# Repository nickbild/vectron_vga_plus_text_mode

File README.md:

# Vectron VGA Plus Text Mode

Vectron VGA Plus Text Mode simplifies displaying text with retro computers and microcontrollers by hiding the pixel-level details.  Supply only row and column positions, and an ASCII character code, to write text to a 40x30 character VGA display.

## How It Works

Vectron VGA Plus Text Mode accepts row, column, and character codes into 8-bit flip flop registers from external systems.  Using a 6502 processor and pre-programmed ROM chip ([code here](https://github.com/nickbild/vectron_vga_plus_text_mode/blob/main/os.asm)), these values are translated into a series of pixels to be drawn at x,y coordinates on the screen.  Both the program, and the library of available ASCII characters are stored in the ROM.  Instructions to draw each pixel are stored in 8-bit flip flop output registers where they can interface with and control a [Vectron VGA Plus](https://github.com/nickbild/vectron_vga_plus) VGA adapter.  Text Mode also handles initialization of a blank screen on the VGA adapter on startup.

To write a single 8x8 character to the screen without Text Mode would require writing 64 individual pixels, and performing all of the associated instructions and data transformations.  This would keep a typical 6502 computer pretty busy just writing to the screen, not to mention all of the other things the computer needs to do.  Text Mode allows for the same result with just a few instructions from the interfacing device.

At the heart of the design is a 65C02 processor to handle the somewhat complex calculations that would be difficult to perform with only logic chips, and would require a high part count.  I think using a microprocessor in this board is well within the bounds of being acceptable for a pure retro computing device, considering that the Commodore 1541 disk drive, for example, also had its own 6502 to handle processing.

An Arudino sketch that can be used to write characters using Text Mode [is here](https://github.com/nickbild/vectron_vga_plus_text_mode/tree/main/ardunio_tester).  KiCad design files are [available here](https://github.com/nickbild/vectron_vga_plus_text_mode/tree/main/kicad).  You will also need a [Vectron VGA Plus](https://github.com/nickbild/vectron_vga_plus) VGA adapter, which Text Mode was designed to work with.

## Media

Vectron VGA Plus Text Mode:

Vectron VGA Plus Text Mode attached to Vectron VGA Plus, with an Arduino Mega 2560 requesting the characters to be written on screen:

All characters in a repeating pattern:

Text mode interface:

Breadboard prototype (with a few components removed to place on the PCB):

## Bill of Materials

- 1 x WDC 65C02 processor
- 1 x AS6C62256A-70PCN 32KB RAM
- 1 x AT28C256-15PU 32KB ROM
- 1 x 8 MHz oscillator
- 4 x 3.3k ohm resistors
- 2 x 220 uF capacitors
- 1 x push button
- 2 x 7432
- 1 x 7408
- 1 x 7404
- 2 x 74682
- 1 x 74154
- 8 x 74374
- Female headers
- PCB ([KiCad design files](https://github.com/nickbild/vectron_vga_plus_text_mode/tree/main/kicad))

## About the Author

[Nick A. Bild, MS](https://nickbild79.firebaseapp.com/#!/)

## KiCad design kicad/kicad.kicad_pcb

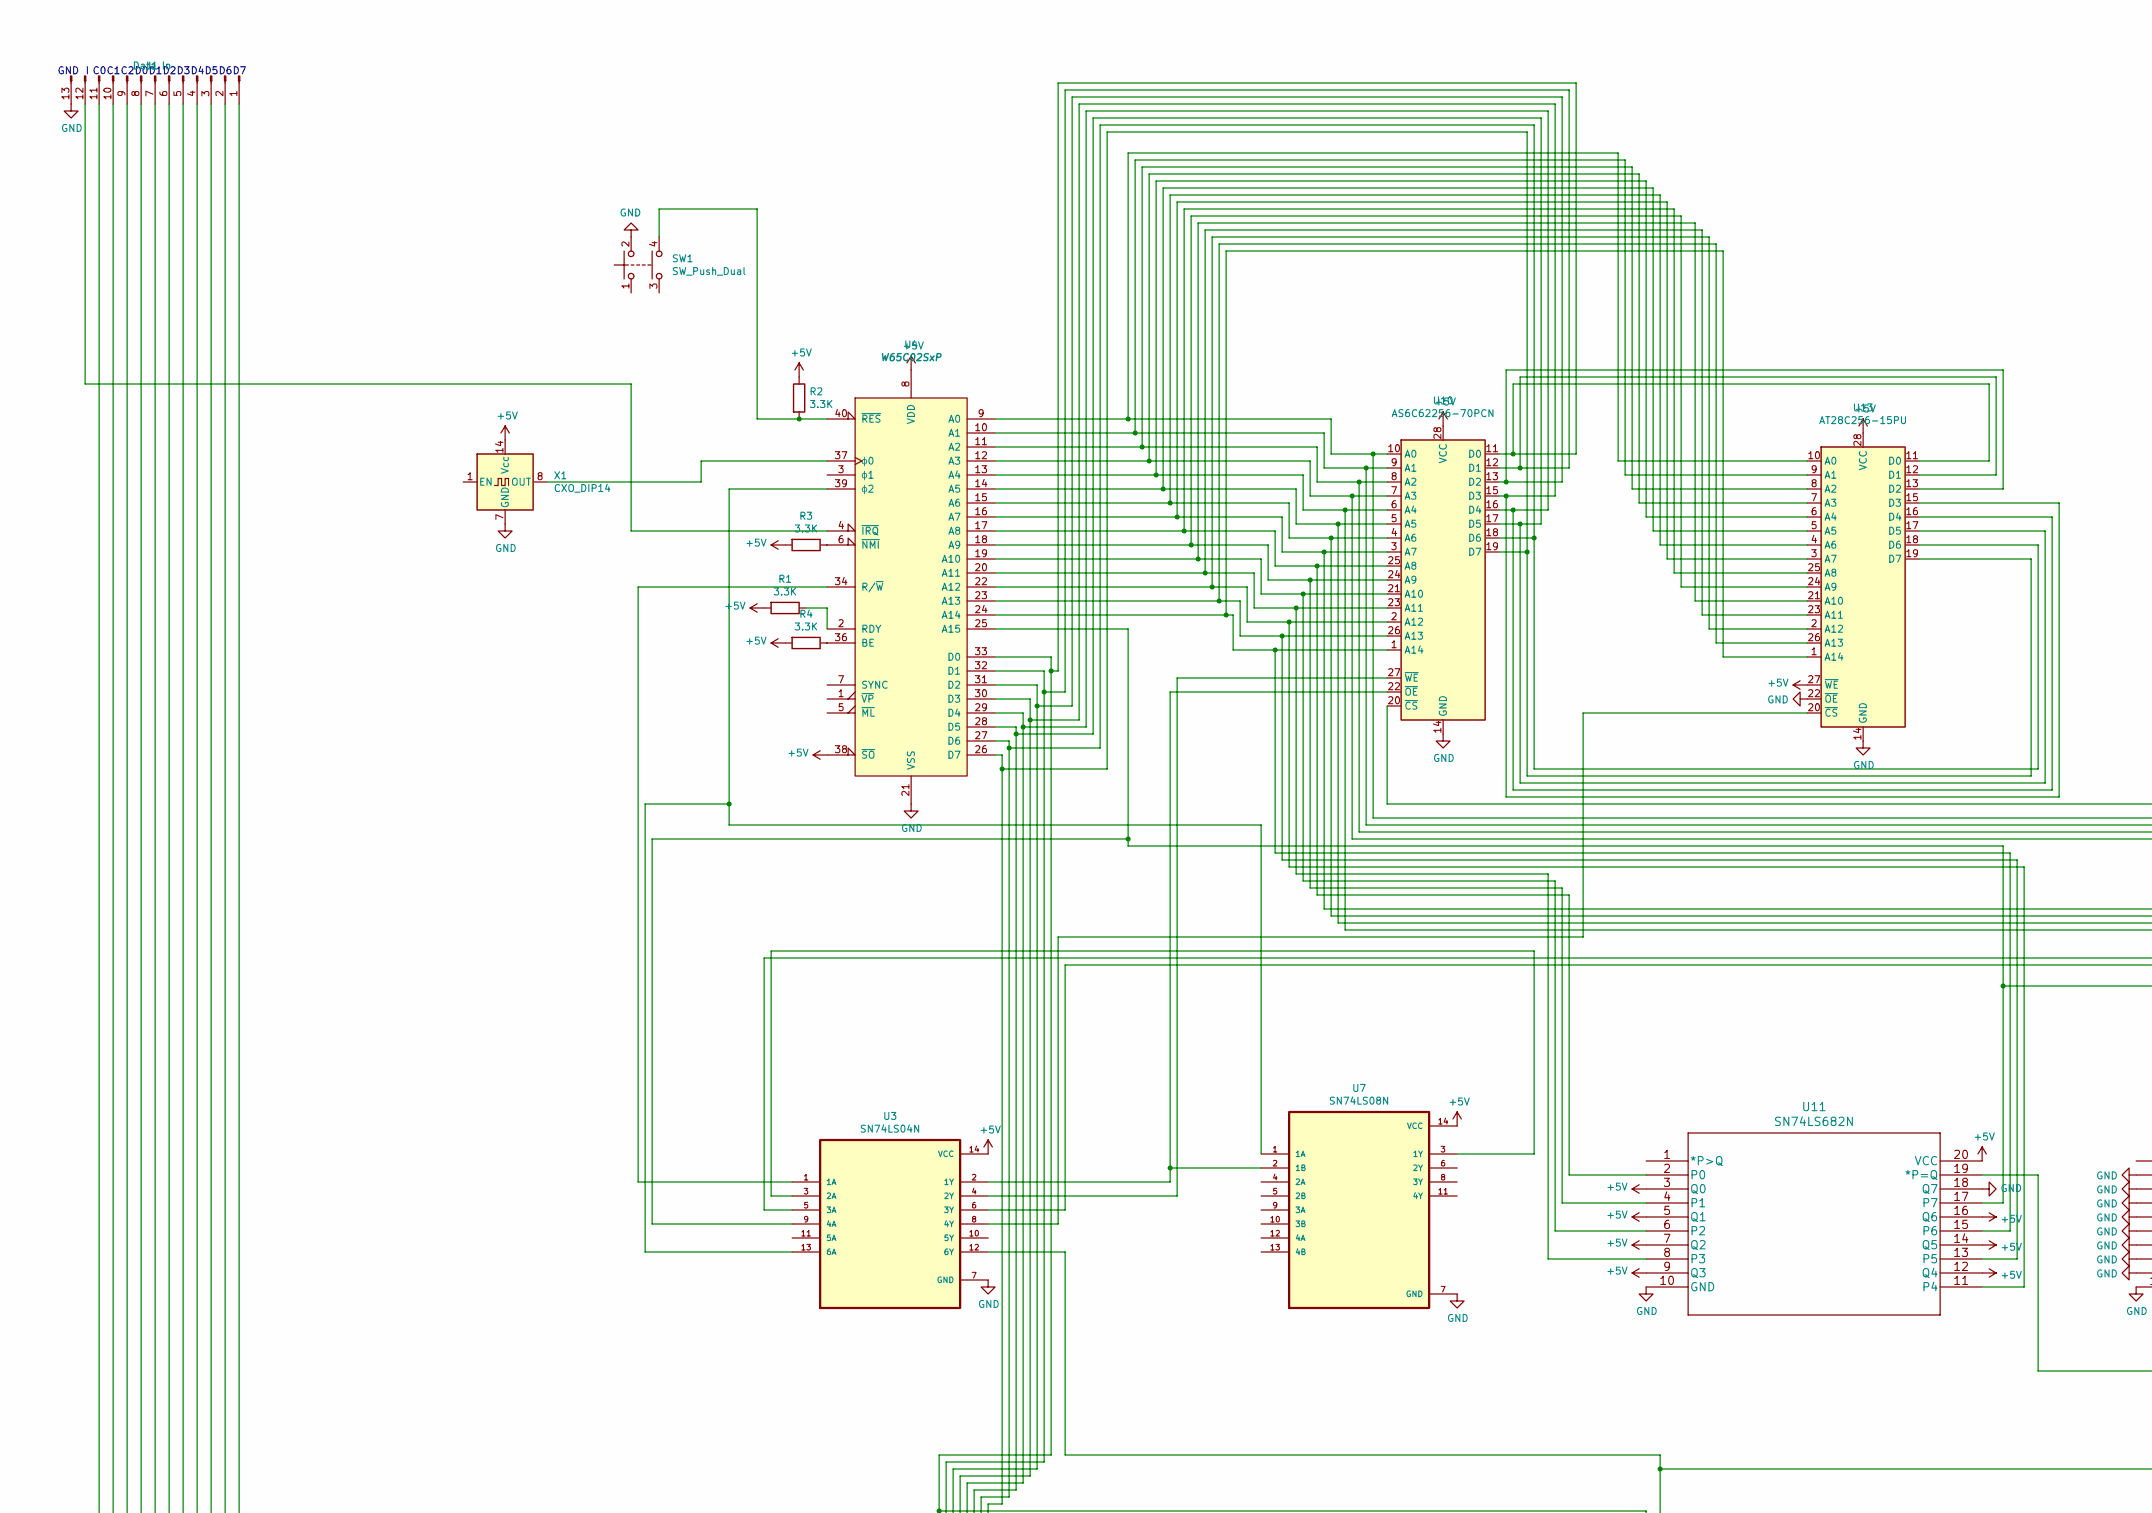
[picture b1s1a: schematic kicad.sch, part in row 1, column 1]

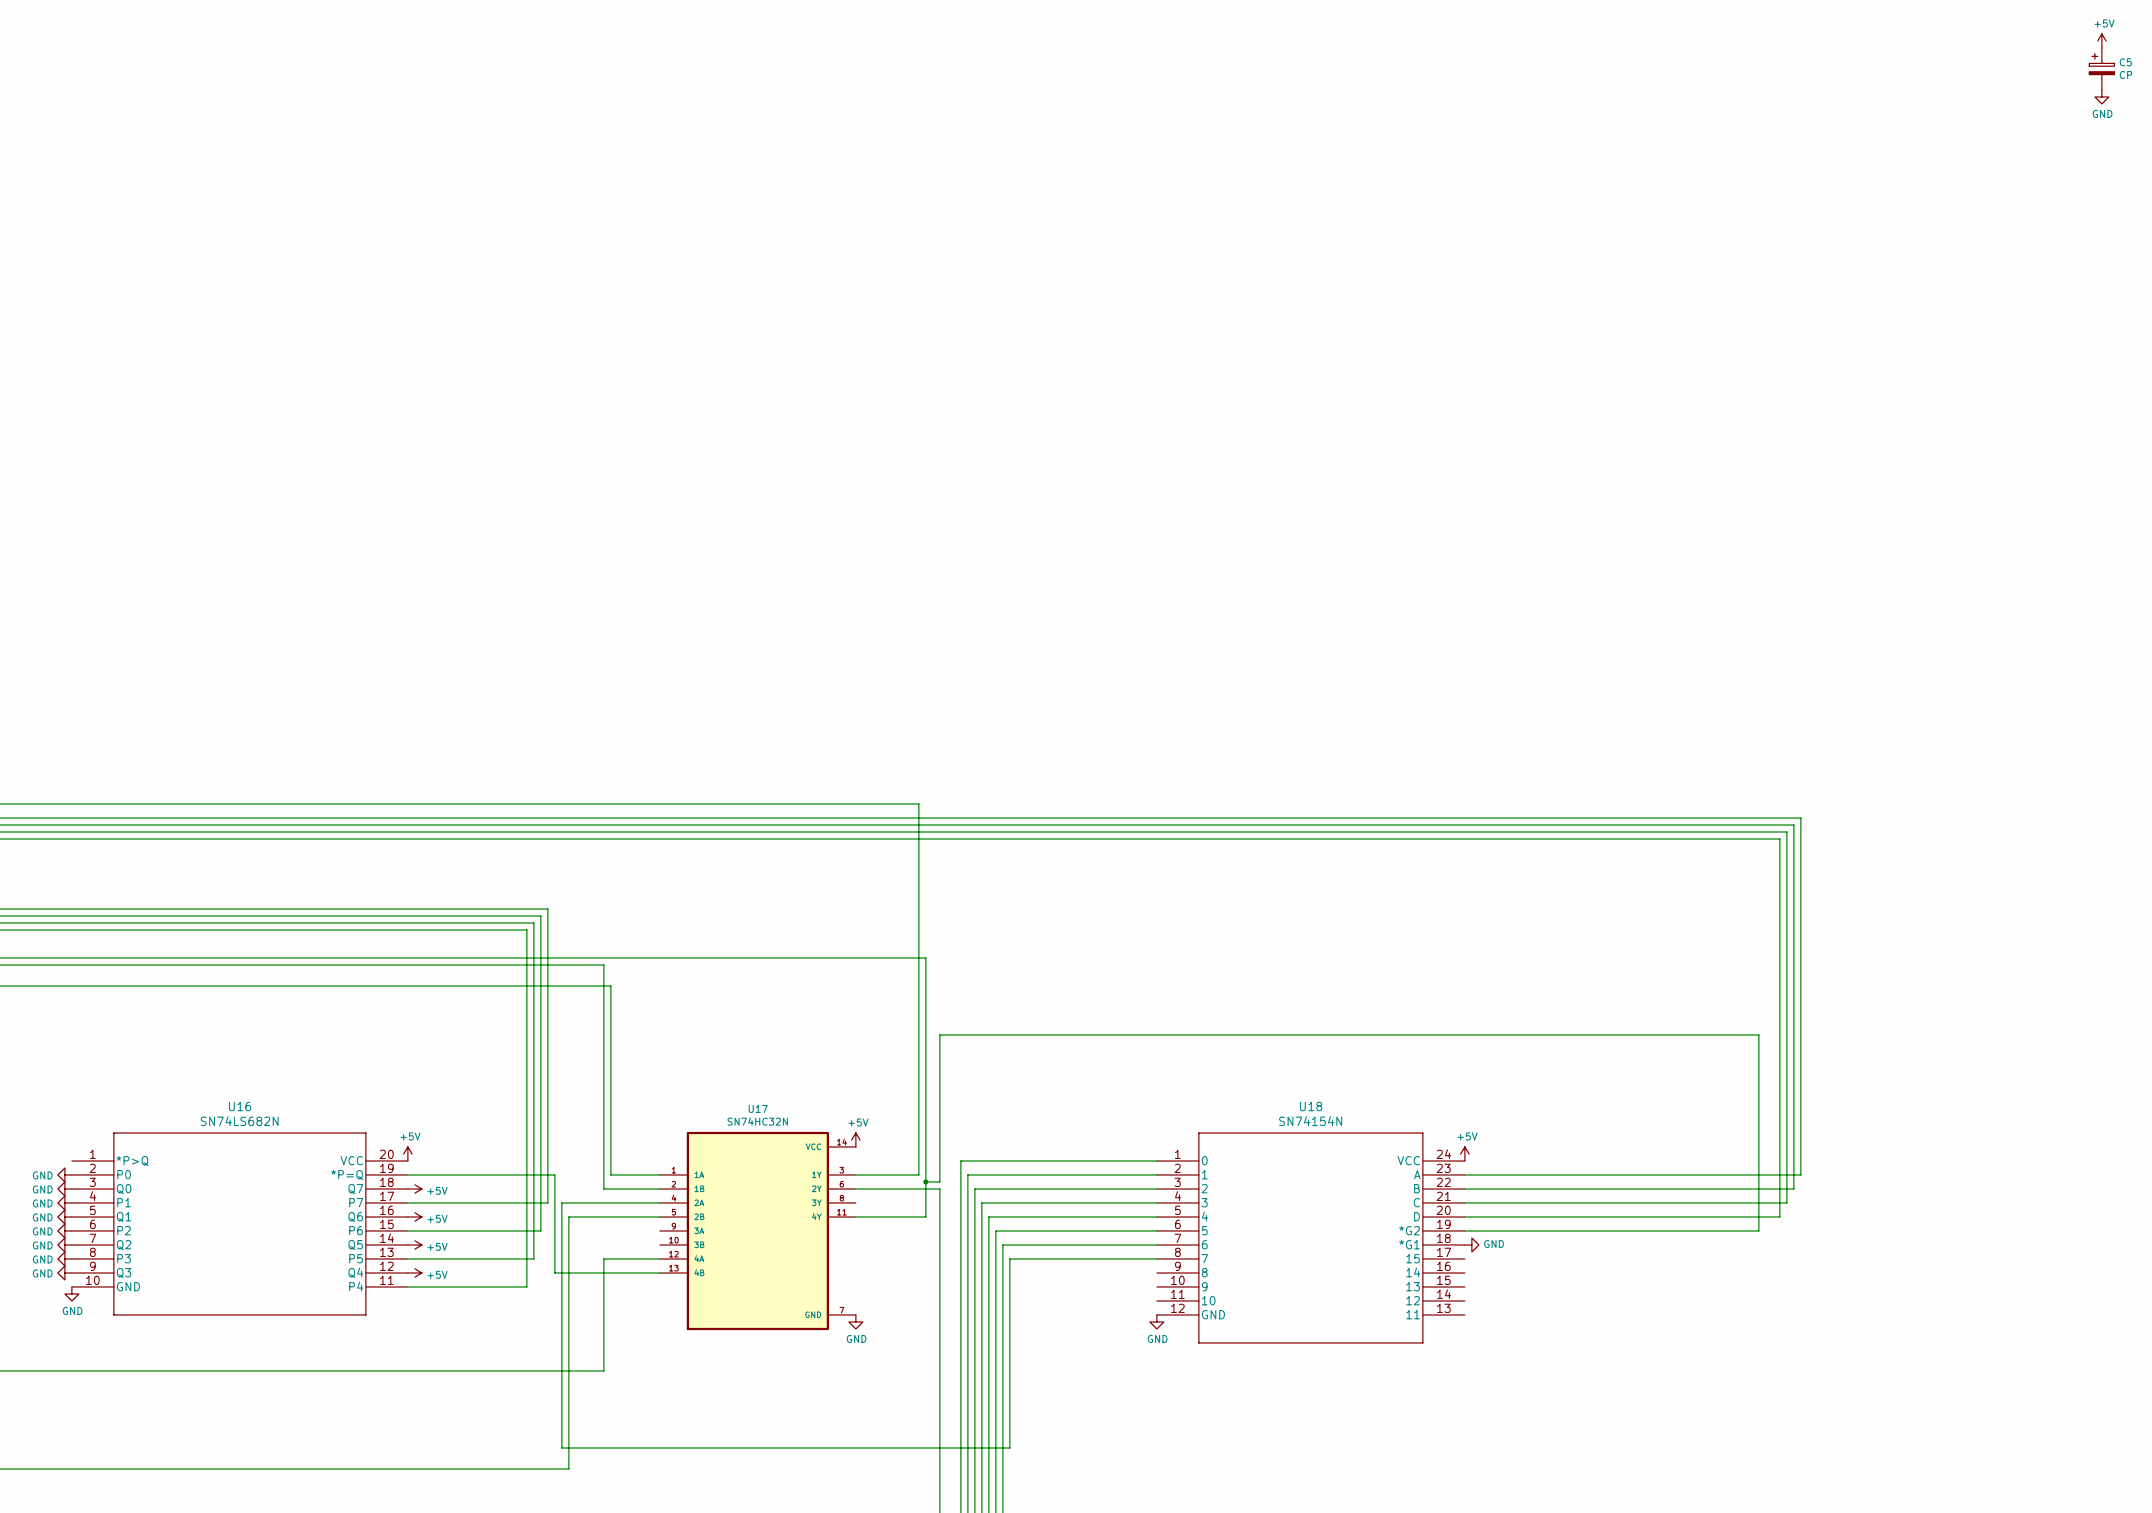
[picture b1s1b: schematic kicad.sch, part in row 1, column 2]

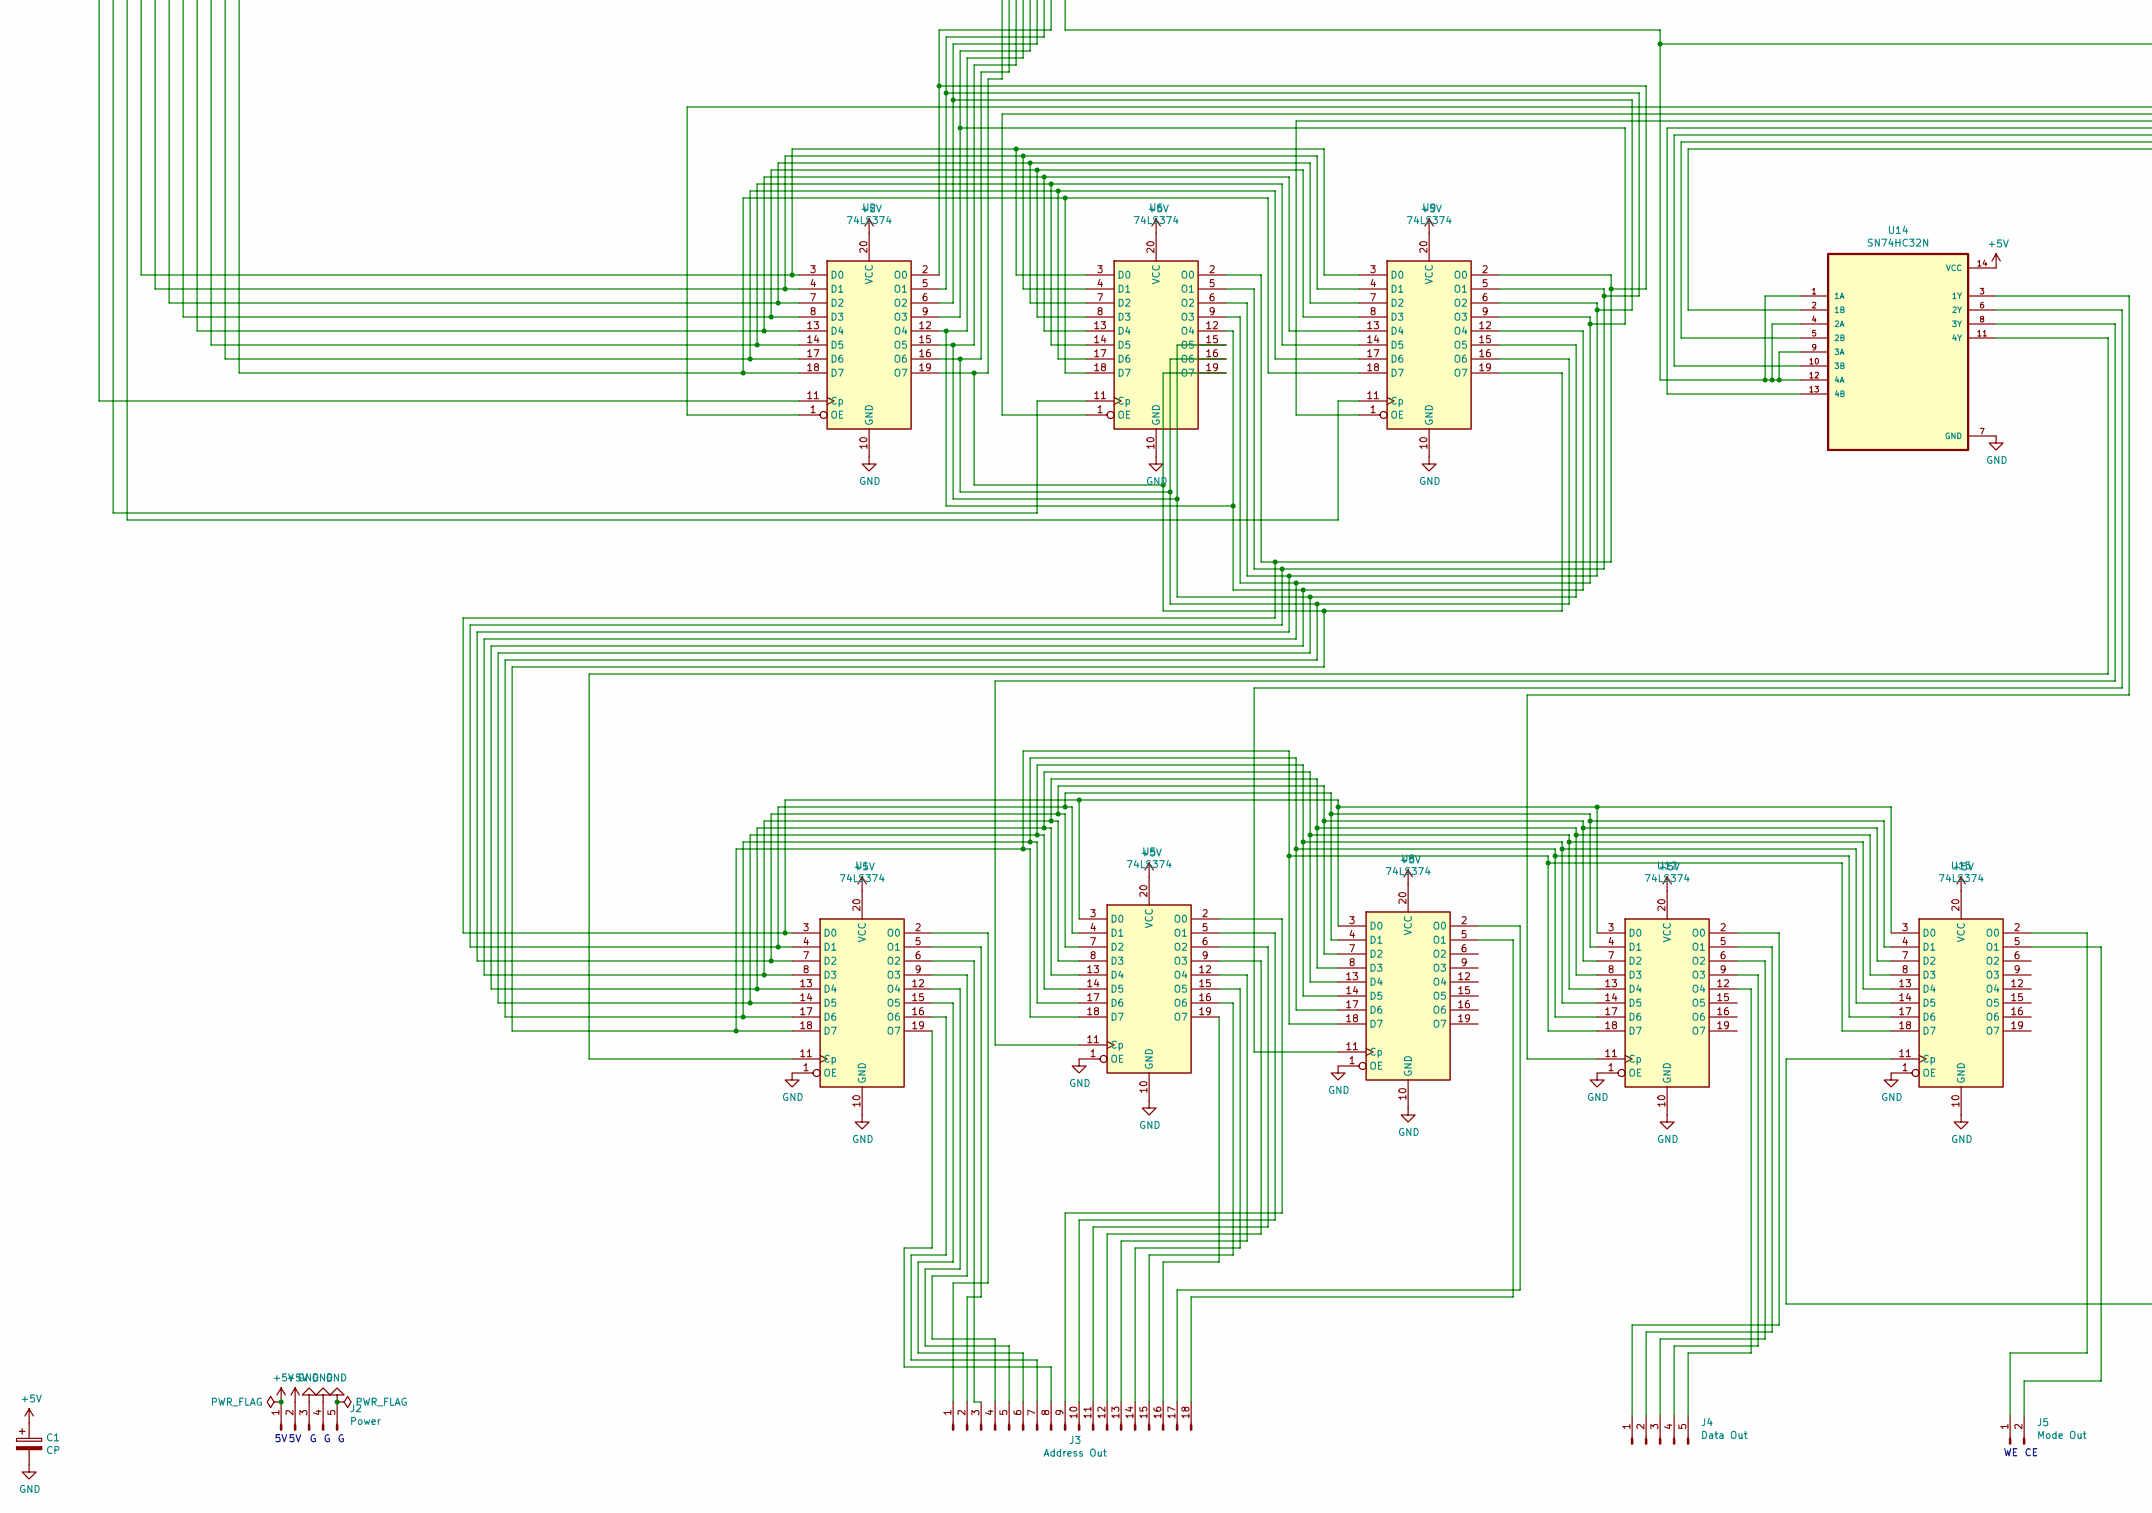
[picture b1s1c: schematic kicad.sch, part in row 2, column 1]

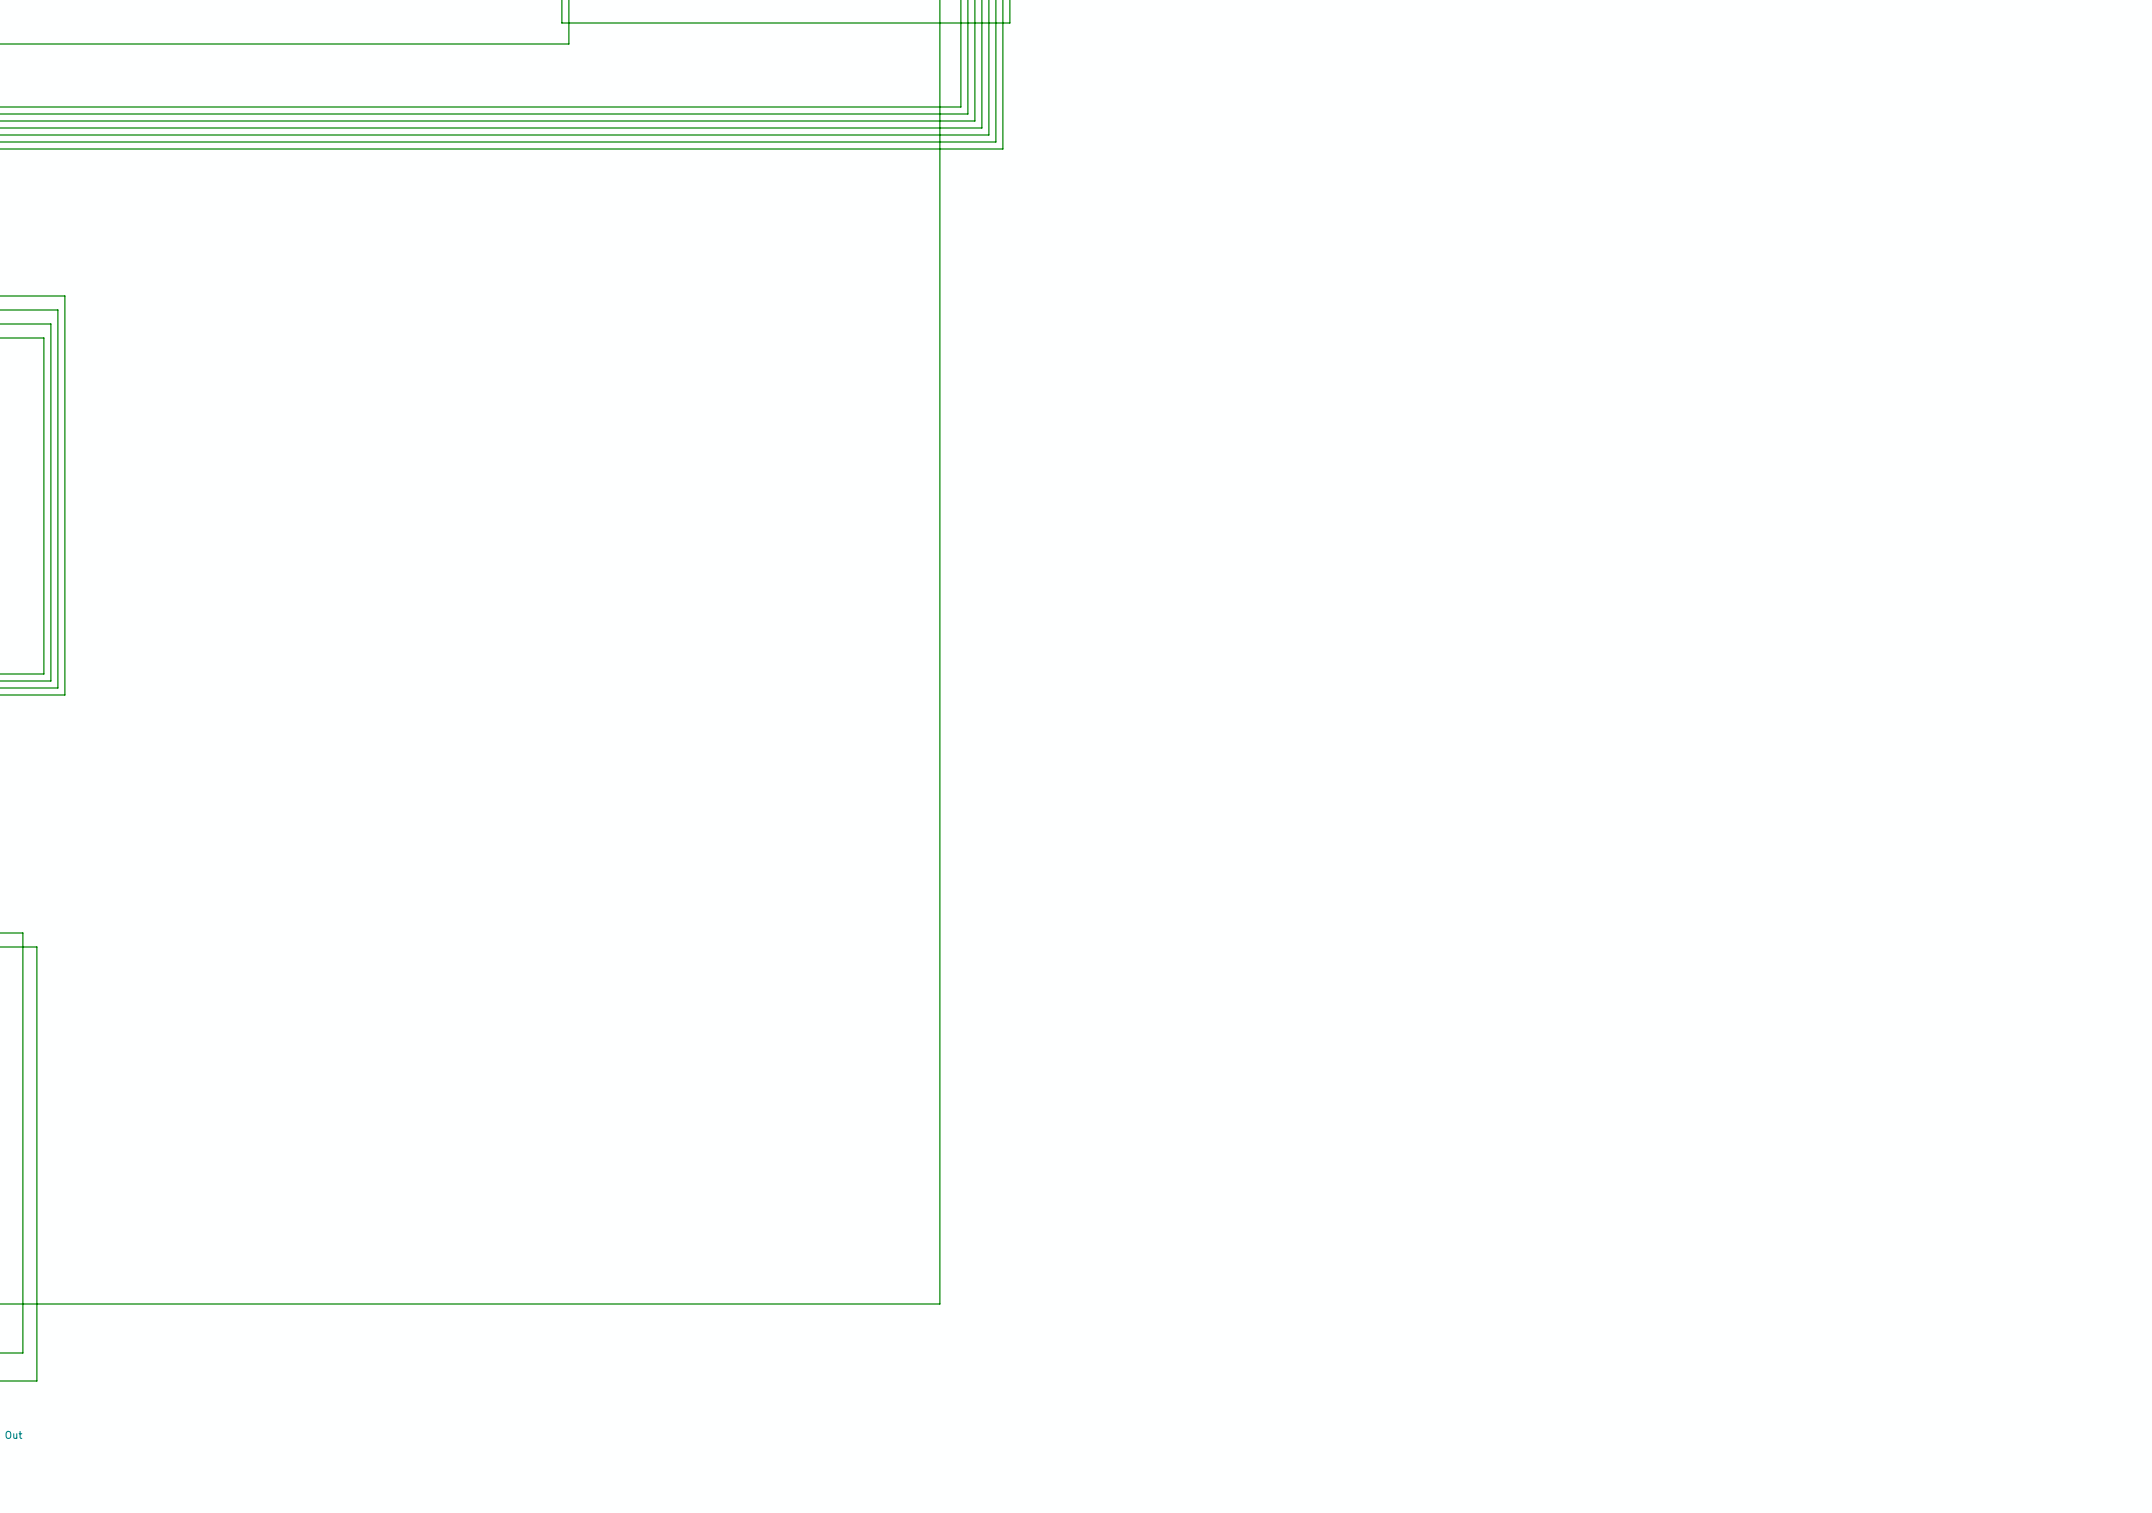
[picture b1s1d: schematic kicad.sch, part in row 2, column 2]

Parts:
C1, C5: CP; CP_Radial_D12.5mm_P7.50mm
J1: Data In; PinHeader_1x13_P2.54mm_Horizontal
J2: Power; PinHeader_1x05_P2.54mm_Horizontal
J3: Address Out; PinHeader_1x18_P2.54mm_Horizontal
J4: Data Out; PinHeader_1x05_P2.54mm_Horizontal
J5: Mode Out; PinHeader_1x02_P2.54mm_Horizontal
R1, R2, R3, R4: 3.3K; R_Axial_DIN0207_L6.3mm_D2.5mm_P10.16mm_Horizontal
SW1: SW_Push_Dual; SW_TH_Tactile_Omron_B3F-10xx
U1, U2, U5, U6, U8, U9, U12, U15: 74LS374; DIP-20_W7.62mm
U3: SN74LS04N; DIP-14_W7.62mm
U4: W65C02SxP; DIP-40_W15.24mm
U7: SN74LS08N; DIP-14_W7.62mm
U10: AS6C62256-70PCN; DIP-28_W15.24mm
U11, U16: SN74LS682N; DIP-20_W7.62mm
U13: AT28C256-15PU; DIP-28_W15.24mm
U14, U17: SN74HC32N; DIP-14_W7.62mm
U18: SN74154N; DIP-24_W15.24mm
X1: CXO_DIP14; Oscillator_DIP-14

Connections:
+5V: C1.1, C5.1, J2.1, J2.2, R1.2, R2.1, R3.2, R4.2, U1.20 (VCC), U2.20 (VCC), U3.14 (VCC), U4.8 (VDD), U4.38 (~SO), U5.20 (VCC), U6.20 (VCC), U7.14 (VCC), U8.20 (VCC), U9.20 (VCC), U10.28 (VCC), U11.3 (Q0), U11.5 (Q1), U11.7 (Q2), U11.9 (Q3), U11.12 (Q4), U11.14 (Q5), U11.16 (Q6), U11.20 (VCC), U12.20 (VCC), U13.27 (~WE), U13.28 (VCC), U14.14 (VCC), U15.20 (VCC), U16.12 (Q4), U16.14 (Q5), U16.16 (Q6), U16.18 (Q7), U16.20 (VCC), U17.14 (VCC), U18.24 (VCC), X1.14 (Vcc)
GND: C1.2, C5.2, J1.13, J2.3, J2.4, J2.5, SW1.2, U1.1 (OE), U1.10 (GND), U2.10 (GND), U3.7 (GND), U4.21 (VSS), U5.1 (OE), U5.10 (GND), U6.10 (GND), U7.7 (GND), U8.1 (OE), U8.10 (GND), U9.10 (GND), U10.14 (GND), U11.10 (GND), U11.18 (Q7), U12.1 (OE), U12.10 (GND), U13.14 (GND), U13.22 (~OE), U14.7 (GND), U15.1 (OE), U15.10 (GND), U16.2 (P0), U16.3 (Q0), U16.4 (P1), U16.5 (Q1), U16.6 (P2), U16.7 (Q2), U16.8 (P3), U16.9 (Q3), U16.10 (GND), U17.7 (GND), U18.12 (GND), U18.18 (*G1), X1.7 (GND)
unnamed: J1.1, U2.18 (D7), U6.18 (D7), U9.18 (D7)
unnamed: J1.2, U2.17 (D6), U6.17 (D6), U9.17 (D6)
unnamed: J1.3, U2.14 (D5), U6.14 (D5), U9.14 (D5)
unnamed: J1.4, U2.13 (D4), U6.13 (D4), U9.13 (D4)
unnamed: J1.5, U2.8 (D3), U6.8 (D3), U9.8 (D3)
unnamed: J1.6, U2.7 (D2), U6.7 (D2), U9.7 (D2)
unnamed: J1.7, U2.4 (D1), U6.4 (D1), U9.4 (D1)
unnamed: J1.8, U2.3 (D0), U6.3 (D0), U9.3 (D0)
unnamed: J1.9, U9.11 (Cp)
unnamed: J1.10, U6.11 (Cp)
unnamed: J1.11, U2.11 (Cp)
unnamed: J1.12, U4.4 (~IRQ)
unnamed: J3.1, U1.2 (O0)
unnamed: J3.2, U1.5 (O1)
unnamed: J3.3, U1.6 (O2)
unnamed: J3.4, U1.9 (O3)
unnamed: J3.5, U1.12 (O4)
unnamed: J3.6, U1.15 (O5)
unnamed: J3.7, U1.16 (O6)
unnamed: J3.8, U1.19 (O7)
unnamed: J3.9, U5.2 (O0)
unnamed: J3.10, U5.5 (O1)
unnamed: J3.11, U5.6 (O2)
unnamed: J3.12, U5.9 (O3)
unnamed: J3.13, U5.12 (O4)
unnamed: J3.14, U5.15 (O5)
unnamed: J3.15, U5.16 (O6)
unnamed: J3.16, U5.19 (O7)
unnamed: J3.17, U8.2 (O0)
unnamed: J3.18, U8.5 (O1)
unnamed: J4.1, U12.2 (O0)
unnamed: J4.2, U12.5 (O1)
unnamed: J4.3, U12.6 (O2)
unnamed: J4.4, U12.9 (O3)
unnamed: J4.5, U12.12 (O4)
unnamed: J5.1, U15.2 (O0)
unnamed: J5.2, U15.5 (O1)
unnamed: R1.1, U4.2 (RDY)
unnamed: R2.2, SW1.4, U4.40 (~RES)
unnamed: R3.1, U4.6 (~NMI)
unnamed: R4.1, U4.36 (BE)
unnamed: U1.3 (D0), U2.2 (O0), U4.33 (D0), U5.3 (D0), U6.2 (O0), U8.3 (D0), U9.2 (O0), U10.11 (D0), U12.3 (D0), U13.11 (D0), U15.3 (D0)
unnamed: U1.4 (D1), U2.5 (O1), U4.32 (D1), U5.4 (D1), U6.5 (O1), U8.4 (D1), U9.5 (O1), U10.12 (D1), U12.4 (D1), U13.12 (D1), U15.4 (D1)
unnamed: U1.7 (D2), U2.6 (O2), U4.31 (D2), U5.7 (D2), U6.6 (O2), U8.7 (D2), U9.6 (O2), U10.13 (D2), U12.7 (D2), U13.13 (D2), U15.7 (D2)
unnamed: U1.8 (D3), U2.9 (O3), U4.30 (D3), U5.8 (D3), U6.9 (O3), U8.8 (D3), U9.9 (O3), U10.15 (D3), U12.8 (D3), U13.15 (D3), U15.8 (D3)
unnamed: U1.11 (Cp), U14.11 (4Y)
unnamed: U1.13 (D4), U2.12 (O4), U4.29 (D4), U5.13 (D4), U6.12 (O4), U8.13 (D4), U9.12 (O4), U10.16 (D4), U12.13 (D4), U13.16 (D4), U15.13 (D4)
unnamed: U1.14 (D5), U2.15 (O5), U4.28 (D5), U5.14 (D5), U6.15 (O5), U8.14 (D5), U9.15 (O5), U10.17 (D5), U12.14 (D5), U13.17 (D5), U15.14 (D5)
unnamed: U1.17 (D6), U2.16 (O6), U4.27 (D6), U5.17 (D6), U6.16 (O6), U8.17 (D6), U9.16 (O6), U10.18 (D6), U12.17 (D6), U13.18 (D6), U15.17 (D6)
unnamed: U1.18 (D7), U2.19 (O7), U4.26 (D7), U5.18 (D7), U6.19 (O7), U8.18 (D7), U9.19 (O7), U10.19 (D7), U12.18 (D7), U13.19 (D7), U15.18 (D7)
unnamed: U3.1 (1A), U4.34 (R/~W)
unnamed: U3.3 (2A), U7.3 (1Y)
unnamed: U3.13 (6A), U4.39 (ϕ2), U7.1 (1A)
unnamed: U4.37 (ϕ0), X1.8 (OUT)
unnamed: U4.24 (A14), U10.1 (A14), U11.15 (P6), U13.1 (A14)
unnamed: U4.22 (A12), U10.2 (A12), U11.11 (P4), U13.2 (A12)
unnamed: U4.16 (A7), U10.3 (A7), U13.3 (A7), U16.17 (P7)
unnamed: U4.15 (A6), U10.4 (A6), U13.4 (A6), U16.15 (P6)
unnamed: U4.14 (A5), U10.5 (A5), U13.5 (A5), U16.13 (P5)
unnamed: U4.13 (A4), U10.6 (A4), U13.6 (A4), U16.11 (P4)
unnamed: U4.12 (A3), U10.7 (A3), U13.7 (A3), U18.20 (D)
unnamed: U4.11 (A2), U10.8 (A2), U13.8 (A2), U18.21 (C)
unnamed: U4.10 (A1), U10.9 (A1), U13.9 (A1), U18.22 (B)
unnamed: U4.9 (A0), U10.10 (A0), U13.10 (A0), U18.23 (A)
unnamed: U10.20 (~CS), U17.3 (1Y)
unnamed: U4.19 (A10), U10.21 (A10), U11.6 (P2), U13.21 (A10)
unnamed: U3.2 (1Y), U7.2 (1B), U10.22 (~OE)
unnamed: U4.20 (A11), U10.23 (A11), U11.8 (P3), U13.23 (A11)
unnamed: U4.18 (A9), U10.24 (A9), U11.4 (P1), U13.24 (A9)
unnamed: U4.17 (A8), U10.25 (A8), U11.2 (P0), U13.25 (A8)
unnamed: U4.23 (A13), U10.26 (A13), U11.13 (P5), U13.26 (A13)
unnamed: U3.4 (2Y), U10.27 (~WE)
unnamed: U3.9 (4A), U4.25 (A15), U11.17 (P7), U17.1 (1A)
unnamed: U11.19 (*P=Q), U17.12 (4A)
unnamed: U12.11 (Cp), U14.3 (1Y)
unnamed: U3.8 (4Y), U13.20 (~CS)
unnamed: U3.12 (6Y), U14.1 (1A), U14.4 (2A), U14.9 (3A), U14.12 (4A), U17.5 (2B)
unnamed: U14.2 (1B), U18.7 (6)
unnamed: U14.5 (2B), U18.6 (5)
unnamed: U8.11 (Cp), U14.6 (2Y)
unnamed: U5.11 (Cp), U14.8 (3Y)
unnamed: U14.10 (3B), U18.5 (4)
unnamed: U14.13 (4B), U18.4 (3)
unnamed: U15.11 (Cp), U17.6 (2Y)
unnamed: U16.19 (*P=Q), U17.13 (4B)
unnamed: U3.6 (3Y), U17.2 (1B)
unnamed: U17.4 (2A), U18.8 (7)
unnamed: U3.5 (3A), U17.11 (4Y), U18.19 (*G2)
unnamed: U2.1 (OE), U18.1 (0)
unnamed: U6.1 (OE), U18.2 (1)
unnamed: U9.1 (OE), U18.3 (2)

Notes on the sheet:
GND

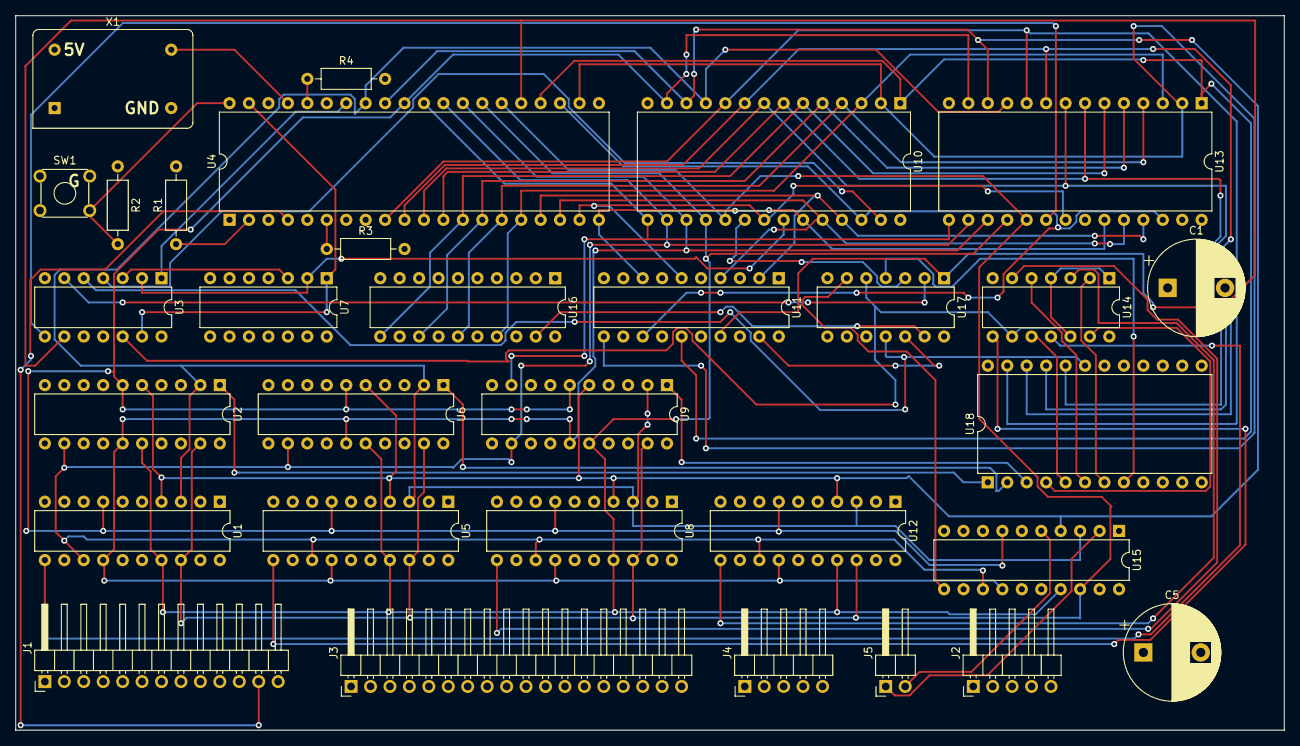
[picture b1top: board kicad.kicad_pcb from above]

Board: 4 copper layers, 165.7 x 93.3 mm, 31 parts (0 on the bottom side), 93 nets.

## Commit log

2021-12-12 Initial commit.
2021-12-12 Generate memory timings for blank VGA screen.
2021-12-16 Save progress.
2021-12-22 Clean up.
2021-12-22 Update documentation.
2021-12-22 Save progress on ISR.
2021-12-31 Change resting control signal state.
2022-01-01 Character definitions working at line level.
2022-01-02 Working at pixel level.
2022-01-02 Disable RAM for full character draw.
2022-01-02 Add character code data to ROM.
2022-01-02 Fix a few character codes.
2022-01-04 Update reserved memory docs.
2022-01-04 Binary values for character definitions.
2022-01-04 Arduino sketch to test text mode.
2022-01-08 Save progress on schematics.
2022-01-17 Finished schematics.
2022-01-18 Save progress on PCB.
2022-01-22 Add gerbers.
2022-02-13 Speed optimized version.
2022-02-14 Update for Vectron VGA output.
2022-02-17 Add upper case character codes.
2022-02-19 Optimize arithmetic for speed.
2022-02-19 Speed optimizations.
2022-02-26 Update for VVGA 2.0.
2022-04-03 Change sync timings.
2022-04-23 Speed up character writes.
2022-04-24 Expand character definitions to increase speed.
2022-04-24 Optimize for speed.
